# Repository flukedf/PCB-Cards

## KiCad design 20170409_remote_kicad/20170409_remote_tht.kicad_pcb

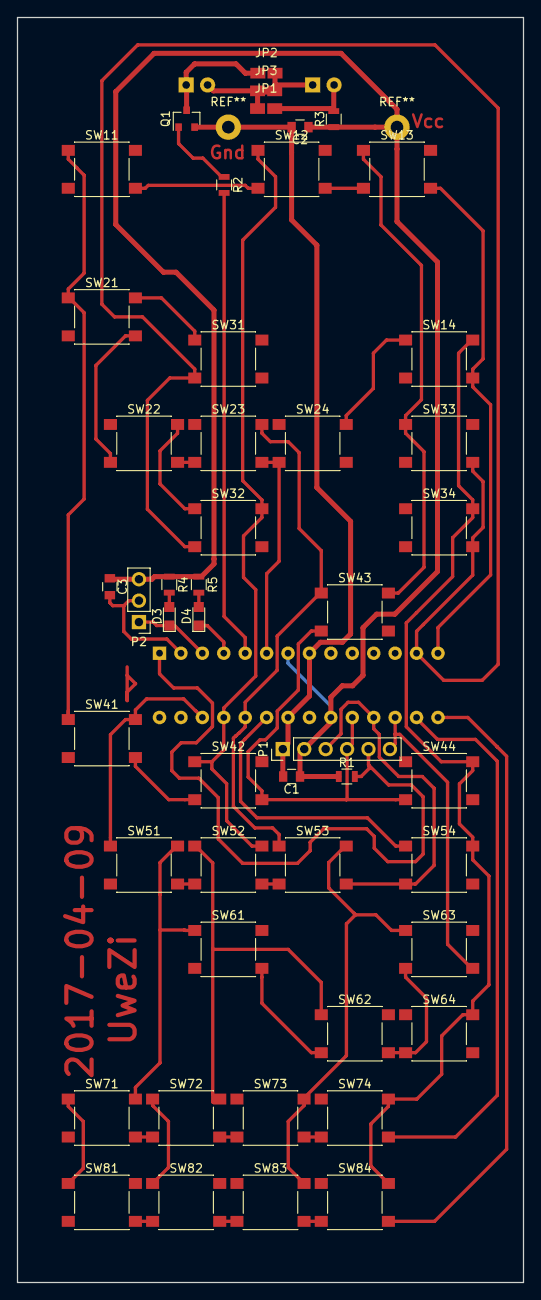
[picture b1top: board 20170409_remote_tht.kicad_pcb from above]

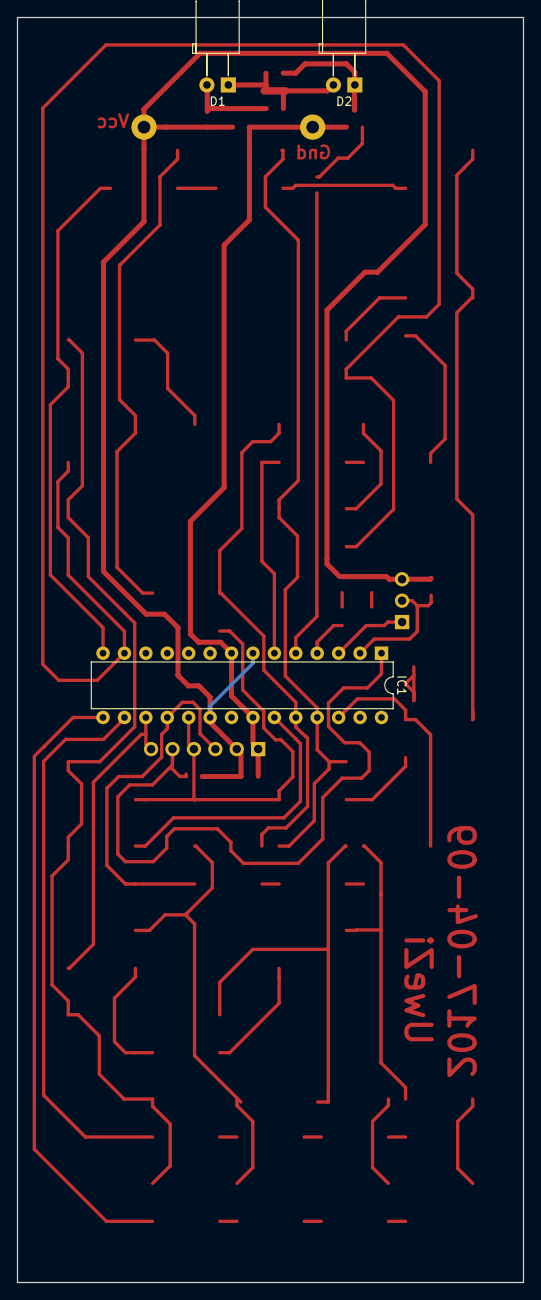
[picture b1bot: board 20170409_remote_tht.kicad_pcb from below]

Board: 2 copper layers, 60.0 x 150.0 mm, 51 parts (3 on the bottom side), 26 nets.

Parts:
C1, C2, C3: C; C_0805
D1, D2: LED; LED_D5.0mm_Horizontal_O3.81mm_Z3.0mm
D3, D4: LED; LED_0805
IC1: ATMEGA328-P; DIP-28_W7.62mm
JP1, JP2: Jumper_NO_Small; net_tie_open
JP3: Jumper_NC_Small; net_tie_closed
P1: CONN_01X06; Socket_Strip_Straight_1x06_Pitch2.54mm
P2: CONN_01X03; Socket_Strip_Straight_1x03_Pitch2.54mm
Q1: MMBT2222; SOT-23
R1, R2, R3, R4, R5: R; R_0805
SW11, SW12, SW13, SW14, SW21, SW22, SW23, SW24, SW31, SW32, SW33, SW34, SW41, SW42, SW43, SW44, SW51, SW52, SW53, SW54, SW61, SW62, SW63, SW64, SW71, SW72, SW73, SW74, SW81, SW82, SW83, SW84: SW_Push_45deg; SW_SPST_PTS645

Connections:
GND: C1.2, C2.2, IC1.8, IC1.22, P1.1, Q1.2
unnamed: D1.1, JP2.1, JP3.1
unnamed: D1.2, JP1.1, R3.2
unnamed: D2.1, JP2.2, Q1.3
unnamed: D2.2, JP1.2, JP3.2
unnamed: D3.2, R4.2
unnamed: D4.2, R5.2
unnamed: Q1.1, R2.1
PB0: IC1.14, SW11.2, SW12.2, SW13.2, SW14.2
PB1: IC1.15, SW81.2, SW82.2, SW83.2, SW84.2
PB2: IC1.16, SW71.2, SW72.2, SW73.2, SW74.2
PB3: IC1.17, P1.6, SW61.2, SW62.2, SW63.2, SW64.2
PB4: IC1.18, P1.3, SW51.2, SW52.2, SW53.2, SW54.2
PB5: IC1.19, P1.4, SW41.2, SW42.2, SW43.2, SW44.2
PC0: IC1.23, SW14.1, SW24.1, SW34.1, SW44.1, SW54.1, SW64.1, SW74.1, SW84.1
PC1: IC1.24, SW13.1, SW23.1, SW33.1, SW43.1, SW53.1, SW63.1, SW73.1, SW83.1
PC2: IC1.25, SW12.1, SW22.1, SW32.1, SW42.1, SW52.1, SW62.1, SW72.1, SW82.1
PC3: IC1.26, SW11.1, SW21.1, SW31.1, SW41.1, SW51.1, SW61.1, SW71.1, SW81.1
PD0: C3.2, IC1.2, P2.2
PD1: D3.1, IC1.3, P2.1
PD2: D4.1, IC1.4
PD3: IC1.5, R2.2
PD4: IC1.6, SW21.2, SW22.2, SW23.2, SW24.2
PD7: IC1.13, SW31.2, SW32.2, SW33.2, SW34.2
RESET: IC1.1, P1.5, R1.2
VCC: C1.1, C2.1, C3.1, IC1.7, IC1.20, P1.2, P2.3, R1.1, R3.1, R4.1, R5.1

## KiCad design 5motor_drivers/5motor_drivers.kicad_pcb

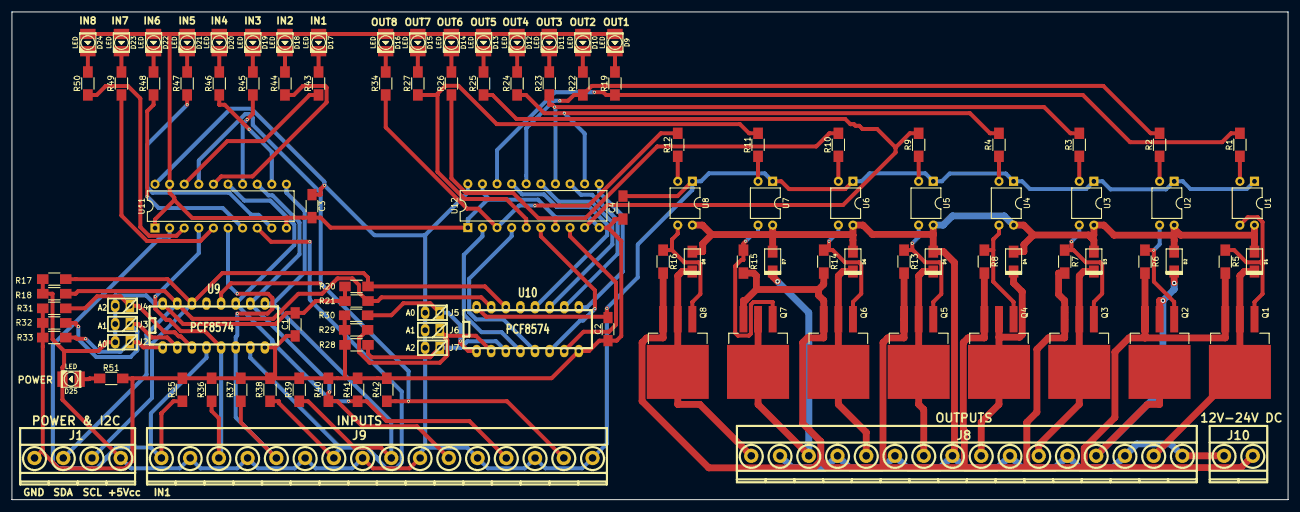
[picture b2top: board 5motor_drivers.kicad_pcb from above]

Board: 2 copper layers, 222.0 x 84.8 mm, 110 parts (0 on the bottom side), 85 nets.

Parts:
C1, C2, C3, C4: 100nF; C_1206_HandSoldering
D1, D2, D3, D4, D5, D6, D7, D8: D; do214ac
D9, D10, D11, D12, D13, D14, D15, D16, D17, D18, D19, D20, D21, D22, D23, D24, D25: LED; Led_PLCC2_3528
J1: POWER & I2C; mkds_1,5-4
J2, J5: A0; pin_strip_2
J3, J6: A1; pin_strip_2
J4, J7: A2; pin_strip_2
J8: OUTPUTS; mkds_1,5-16
J9: INPUTS; mkds_1,5-16
J10: 12V-24V DC; mkds_1,5-2
Q1, Q2, Q3, Q4, Q5, Q6, Q7, Q8: IRF540N; TO-263-3Lead
R1, R2, R3, R4, R9, R10, R11, R12: 470; R_1206_HandSoldering
R5, R6, R7, R8, R13, R14, R15, R16, R17, R18, R20, R21: 10K; R_1206_HandSoldering
R19, R22, R23, R24, R25, R26, R27, R34, R43, R44, R45, R46, R47, R48, R49, R50, R51: 330; R_1206_HandSoldering
R28, R29, R30, R31, R32, R33, R35, R36, R37, R38, R39, R40, R41, R42: 1K; R_1206_HandSoldering
U1, U2, U3, U4, U5, U6, U7, U8: PC817; DIP-4_W7.62mm
U9, U10: PCF8574; dil_16-300
U11, U12: 74LS244; DIP-20_W7.62mm

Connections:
+5Vcc: C1.2, C2.2, C3.1, C4.1, D25.2, J1.4, J2.2, J3.2, J4.2, J5.2, J6.2, J7.2, J9.2, J9.4, J9.6, J9.8, J9.10, J9.12, J9.14, J9.16, R17.1, R18.1, R20.1, R21.1, U1.1, U2.1, U3.1, U4.1, U5.1, U6.1, U7.1, U8.1, U9.16, U10.16, U11.20, U12.20
+24V: D1.1, D2.1, D3.1, D4.1, D5.1, D6.1, D7.1, D8.1, J8.2, J8.4, J8.6, J8.8, J8.10, J8.12, J8.14, J8.16, J10.1, U1.4, U2.4, U3.4, U4.4, U5.4, U6.4, U7.4, U8.4
GND: C1.1, C2.1, C3.2, C4.2, D9.1, D10.1, D11.1, D12.1, D13.1, D14.1, D15.1, D16.1, D17.1, D18.1, D19.1, D20.1, D21.1, D22.1, D23.1, D24.1, J1.1, R28.2, R29.2, R30.2, R31.2, R32.2, R33.2, R35.2, R36.2, R37.2, R38.2, R39.2, R40.2, R41.2, R42.2, R51.2, U9.8, U10.8, U11.1, U11.10, U11.19, U12.1, U12.10, U12.19
GNDPWR: J10.2, Q1.3, Q2.3, Q3.3, Q4.3, Q5.3, Q6.3, Q7.3, Q8.3, R5.2, R6.2, R7.2, R8.2, R13.2, R14.2, R15.2, R16.2
IN01: J9.1, R35.1, U9.4, U11.2
IN02: J9.3, R36.1, U9.5, U11.4
IN03: J9.5, R37.1, U9.6, U11.6
IN04: J9.7, R38.1, U9.7, U11.8
IN05: J9.9, R39.1, U9.9, U11.11
IN06: J9.11, R40.1, U9.10, U11.13
IN07: J9.13, R41.1, U9.11, U11.15
IN08: J9.15, R42.1, U9.12, U11.17
MOTOR_01-: D1.2, J8.15, Q1.2
MOTOR_02-: D2.2, J8.13, Q2.2
MOTOR_03-: D3.2, J8.11, Q3.2
MOTOR_04-: D4.2, J8.9, Q4.2
MOTOR_05-: D5.2, J8.7, Q5.2
MOTOR_06-: D6.2, J8.5, Q6.2
MOTOR_07-: D7.2, J8.3, Q7.2
MOTOR_08-: D8.2, J8.1, Q8.2
unnamed: D9.2, R19.2
unnamed: D10.2, R22.2
unnamed: D11.2, R23.2
unnamed: D12.2, R24.2
unnamed: D13.2, R25.2
unnamed: D14.2, R26.2
unnamed: D15.2, R27.2
unnamed: D16.2, R34.2
unnamed: D17.2, R43.2
unnamed: D18.2, R44.2
unnamed: D19.2, R45.2
unnamed: D20.2, R46.2
unnamed: D21.2, R47.2
unnamed: D22.2, R48.2
unnamed: D23.2, R49.2
unnamed: D24.2, R50.2
unnamed: D25.1, R51.1
unnamed: J2.1, R33.1, U9.1
unnamed: J3.1, R32.1, U9.2
unnamed: J4.1, R31.1, U9.3
unnamed: J5.1, R30.1, U10.1
unnamed: J6.1, R29.1, U10.2
unnamed: J7.1, R28.1, U10.3
unnamed: Q1.1, R5.1, U1.3
unnamed: Q2.1, R6.1, U2.3
unnamed: Q3.1, R7.1, U3.3
unnamed: Q4.1, R8.1, U4.3
unnamed: Q5.1, R13.1, U5.3
unnamed: Q6.1, R14.1, U6.3
unnamed: Q7.1, R15.1, U7.3
unnamed: Q8.1, R16.1, U8.3
unnamed: R1.1, U1.2
unnamed: R2.1, U2.2
unnamed: R3.1, U3.2
unnamed: R4.1, U4.2
unnamed: R9.1, U5.2
unnamed: R10.1, U6.2
unnamed: R11.1, U7.2
unnamed: R12.1, U8.2
Q1: R1.2, R19.1, U12.18
Q2: R2.2, R22.1, U12.16
Q3: R3.2, R23.1, U12.14
Q4: R4.2, R24.1, U12.12
Q5: R9.2, R25.1, U12.9
Q6: R10.2, R26.1, U12.7
Q7: R11.2, R27.1, U12.5
Q8: R12.2, R34.1, U12.3
S1: R43.1, U11.18
S2: R44.1, U11.16
S3: R45.1, U11.14
S4: R46.1, U11.12
S5: R47.1, U11.9
S6: R48.1, U11.7
S7: R49.1, U11.5
S8: R50.1, U11.3
SCL: J1.3, R17.2, R20.2, U9.14, U10.14
SDA: J1.2, R18.2, R21.2, U9.15, U10.15
SIGNAL_01: U10.4, U12.2
SIGNAL_02: U10.5, U12.4
SIGNAL_03: U10.6, U12.6
SIGNAL_04: U10.7, U12.8
SIGNAL_05: U10.9, U12.11
SIGNAL_06: U10.10, U12.13
SIGNAL_07: U10.11, U12.15
SIGNAL_08: U10.12, U12.17

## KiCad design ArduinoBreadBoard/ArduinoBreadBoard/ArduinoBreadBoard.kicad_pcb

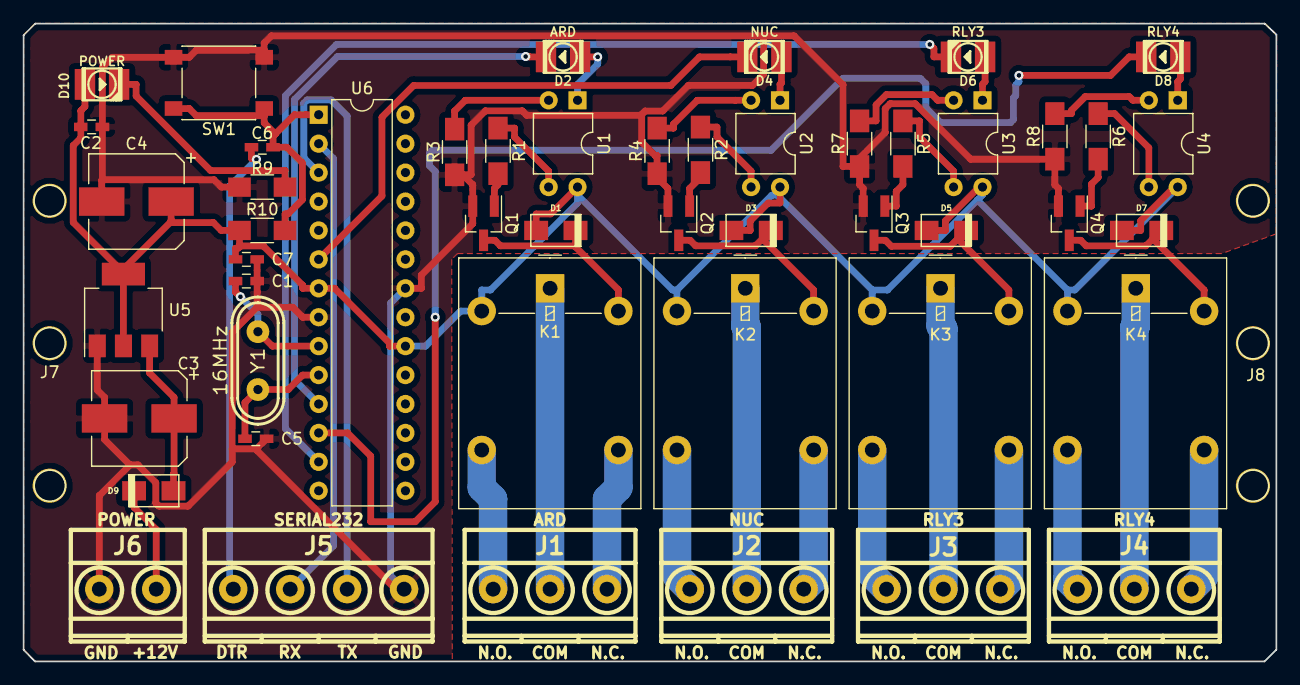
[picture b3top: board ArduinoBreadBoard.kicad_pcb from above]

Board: 2 copper layers, 110.0 x 56.0 mm, 51 parts (0 on the bottom side), 47 nets.

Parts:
C1, C5: 22pF; C_0603_HandSoldering
C2, C7: 100nF; C_0603_HandSoldering
C3, C4: 47uF; CP_Elec_8x6.5
C6: 0.1uF; C_0603_HandSoldering
D1, D3, D5, D7, D9: 1N4001; do214ac
D2: ARD; Led_PLCC2_3528
D4: NUC; Led_PLCC2_3528
D6: RLY3; Led_PLCC2_3528
D8: RLY4; Led_PLCC2_3528
D10: POWER; Led_PLCC2_3528
J1: ARD; mkds_1,5-3
J2: NUC; mkds_1,5-3
J3: RLY3; mkds_1,5-3
J4: RLY4; mkds_1,5-3
J5: SERIAL232; mkds_1,5-4
J6: POWER; mkds_1,5-2
J7, J8: hole; Bracket_RielDin_hole
K1, K2, K3, K4: JS1-5V-F
Q1, Q2, Q3, Q4: MMBT5551L; SOT-23_Handsoldering
R1, R2, R5, R6, R10: 10K; R_1206_HandSoldering
R3, R4, R7, R8: 1K; R_1206_HandSoldering
R9: 330; R_1206_HandSoldering
SW1: RESET; SW_SPST_PTS645
U1, U2, U3, U4: PC817; DIP-4_W7.62mm
U5: AMS1117-5.0; SOT-223-3Lead_TabPin2
U6: ATmega328P-PU; DIP-28_W7.62mm
Y1: 16MHz; crystal_hc-49s

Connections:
+5V: C2.1, C4.1, C7.1, D1.1, D3.1, D5.1, D7.1, D10.1, K1.2, K2.2, K3.2, K4.2, R10.1, U1.4, U2.4, U3.4, U4.4, U5.2, U6.7, U6.20
+12V: C3.1, D9.1, U5.3
D4: D4.2, U6.6
D5: D2.2, U6.11
D6: D8.2, U6.12
D7: D6.2, U6.13
DTR: C6.1, J5.1
GND: C1.1, C2.2, C3.2, C4.2, C5.1, C7.2, J5.4, J6.1, Q1.2, Q2.2, Q3.2, Q4.2, R3.1, R4.1, R7.1, R8.1, R9.2, SW1.2, U5.1, U6.8, U6.22
unnamed: C1.2, U6.9, Y1.1
unnamed: C5.2, U6.10, Y1.2
unnamed: C6.2, R10.2, SW1.1, U6.1
unnamed: D1.2, K1.5, Q1.3
unnamed: D2.1, U1.1
unnamed: D3.2, K2.5, Q2.3
unnamed: D4.1, U2.1
unnamed: D5.2, K3.5, Q3.3
unnamed: D6.1, U3.1
unnamed: D7.2, K4.5, Q4.3
unnamed: D8.1, U4.1
unnamed: D9.2, J6.2
unnamed: D10.2, R9.1
unnamed: J1.1, K1.3
unnamed: J1.2, K1.1
unnamed: J1.3, K1.4
unnamed: J2.1, K2.3
unnamed: J2.2, K2.1
unnamed: J2.3, K2.4
unnamed: J3.1, K3.3
unnamed: J3.2, K3.1
unnamed: J3.3, K3.4
unnamed: J4.1, K4.3
unnamed: J4.2, K4.1
unnamed: J4.3, K4.4
unnamed: Q1.1, R1.2
unnamed: Q2.1, R2.2
unnamed: Q3.1, R5.2
unnamed: Q4.1, R6.2
unnamed: R1.1, U1.3
unnamed: R2.1, U2.3
unnamed: R3.2, U1.2
unnamed: R4.2, U2.2
unnamed: R5.1, U3.3
unnamed: R6.1, U4.3
unnamed: R7.2, U3.2
unnamed: R8.2, U4.2
Rx: J5.2, U6.2
Tx: J5.3, U6.3

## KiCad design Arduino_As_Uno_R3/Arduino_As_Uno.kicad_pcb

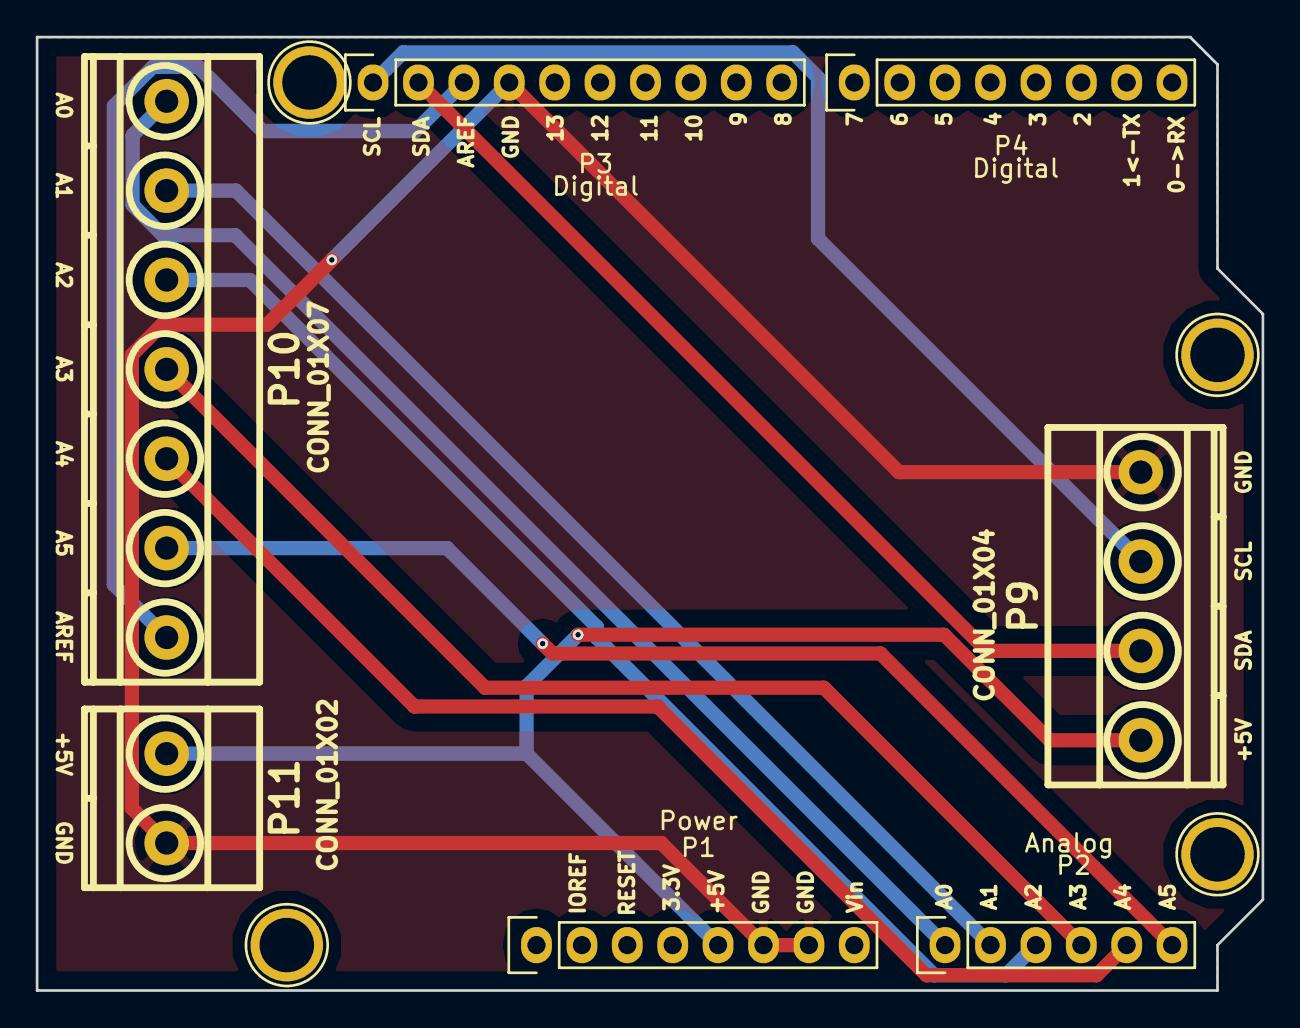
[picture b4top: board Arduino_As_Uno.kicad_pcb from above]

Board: 2 copper layers, 68.6 x 53.3 mm, 11 parts (0 on the bottom side), 11 nets.

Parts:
P1: Power; Socket_Strip_Arduino_1x08
P2: Analog; Socket_Strip_Arduino_1x06
P3: Digital; Socket_Strip_Arduino_1x10
P4: Digital; Socket_Strip_Arduino_1x08
P5, P6, P7, P8: CONN_01X01; Arduino_1pin
P9: CONN_01X04; mkds_1,5-4
P10: CONN_01X07; mkds_1,5-7
P11: CONN_01X02; mkds_1,5-2

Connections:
+5V: P1.5, P9.1, P11.1
/(SCL): P3.1, P9.3
/(SDA): P3.2, P9.2
/A0: P2.1, P10.1
/A1: P2.2, P10.2
/A2: P2.3, P10.3
/A3: P2.4, P10.4
/A4: P2.5, P10.5
/A5: P2.6, P10.6
/AREF: P3.3, P10.7
GND: P1.6, P1.7, P3.4, P9.4, P11.2

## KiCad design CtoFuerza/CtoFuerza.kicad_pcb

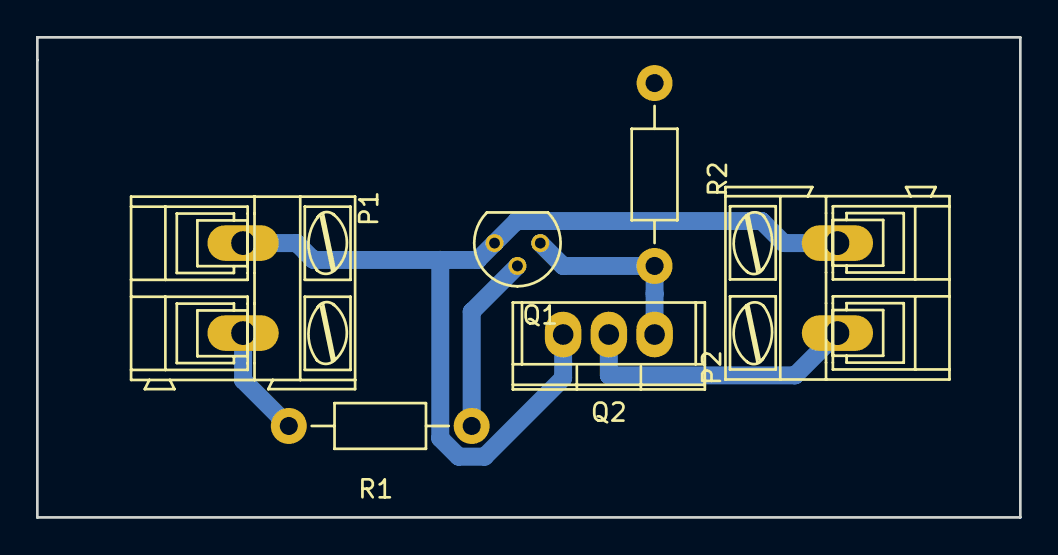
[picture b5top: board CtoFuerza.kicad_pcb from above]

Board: 2 copper layers, 54.6 x 26.7 mm, 6 parts (0 on the bottom side), 5 nets.

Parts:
P1, P2: CONN_01X02; AK300-2
Q1: BC548; TO-92_Molded_Narrow
Q2: IRF540N; TO-220
R1, R2: R; Resistor_Horizontal_RM10mm

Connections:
GND: P1.1, P2.2, Q1.3, Q2.3
unnamed: P1.2, R1.2
unnamed: P2.1, Q2.2
unnamed: Q1.1, Q2.1, R2.2
unnamed: Q1.2, R1.1

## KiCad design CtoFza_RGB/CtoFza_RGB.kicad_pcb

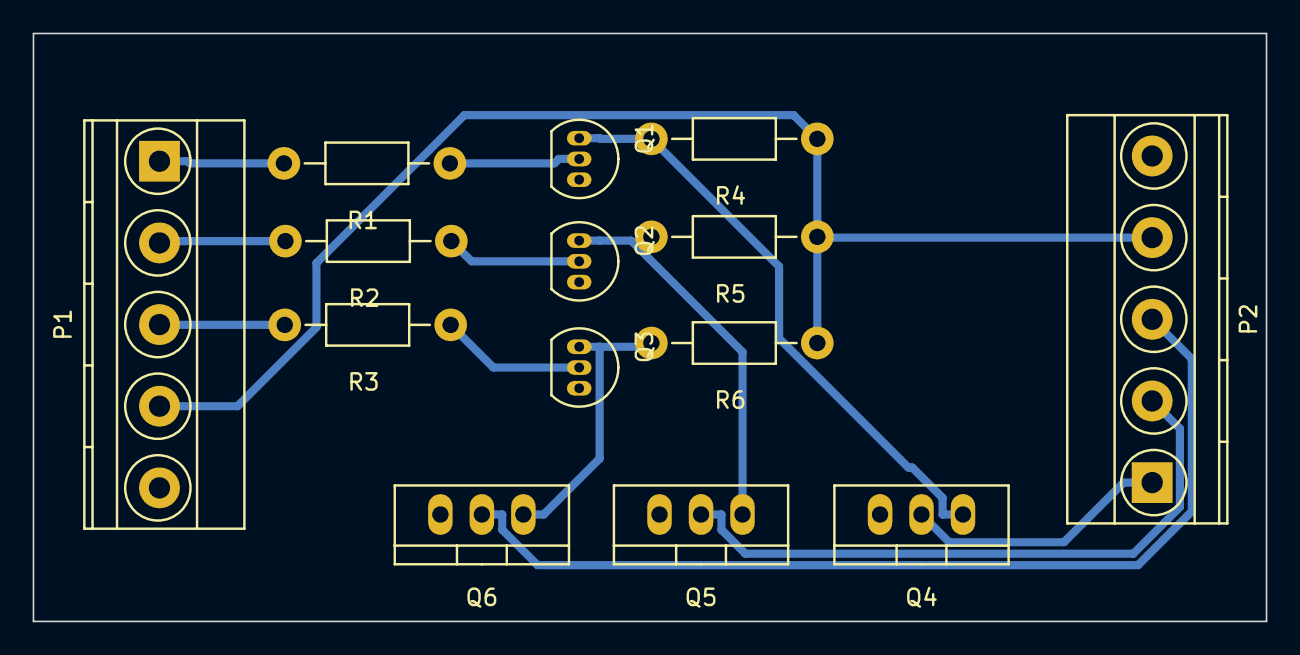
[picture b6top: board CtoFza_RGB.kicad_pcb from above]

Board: 2 copper layers, 75.5 x 36.0 mm, 14 parts (0 on the bottom side), 14 nets.

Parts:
P1: INPUT; TerminalBlock_Pheonix_MKDS1.5-5pol
P2: OUTPUT; TerminalBlock_Pheonix_MKDS1.5-5pol
Q1, Q2, Q3: BC548; TO-92_Inline_Narrow_Oval
Q4, Q5, Q6: IRF540N; TO-220_Neutral123_Vertical
R1, R2, R3, R4, R5, R6: 10K; Resistor_Horizontal_RM10mm

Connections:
12VCD: P1.4, P2.4, R4.1, R5.1, R6.1
B_IN: P1.3, R3.2
B_OUT: P2.3, Q6.2
GND: P1.5, P2.5, Q1.3, Q2.3, Q3.3, Q4.3, Q5.3, Q6.3
G_IN: P1.2, R2.2
G_OUT: P2.2, Q5.2
unnamed: Q1.1, Q4.1, R4.2
unnamed: Q1.2, R1.1
unnamed: Q2.1, Q5.1, R5.2
unnamed: Q2.2, R2.1
unnamed: Q3.1, Q6.1, R6.2
unnamed: Q3.2, R3.1
R_IN: P1.1, R1.2
R_OUT: P2.1, Q4.2

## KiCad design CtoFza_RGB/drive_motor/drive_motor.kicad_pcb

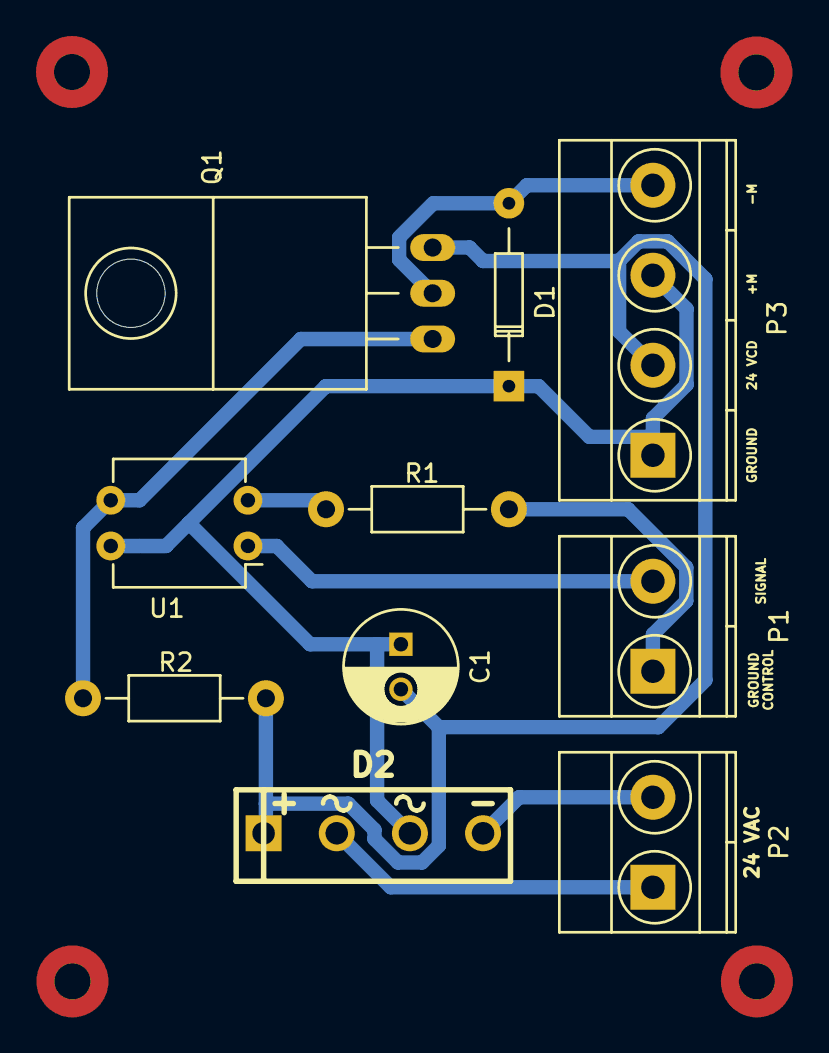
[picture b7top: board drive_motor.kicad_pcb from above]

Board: 2 copper layers, 14 parts (0 on the bottom side), 9 nets.

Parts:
C1: 100uF; C_Radial_D6.3_L11.2_P2.5
D1: 1N4001; Diode_DO-35_SOD27_Horizontal_RM10
D2: KPB206; bridge_2KBP
HOLE-M2, HOLE-M2#2, HOLE-M2#3, HOLE-M2#4: VAL**; HOLE-M2-COND
P1, P2: CONN_01X02; TerminalBlock_Pheonix_MKDS1.5-2pol
P3: CONN_01X04; TerminalBlock_Pheonix_MKDS1.5-4pol
Q1: IRF540N; TO-220_Neutral123_Horizontal
R1: 470; Resistor_Horizontal_RM10mm
R2: 10K; Resistor_Horizontal_RM10mm
U1: PC817; DIP-4_W7.62mm

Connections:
GND: C1.2, D2.1, P3.2, Q1.3, R2.2
GND_CTRL: P1.1, R1.2
MOTOR+: C1.1, D1.1, D2.3, P3.1, P3.3, U1.4
MOTOR-: D1.2, P3.4, Q1.2
unnamed: D2.2, P2.1
unnamed: D2.4, P2.2
unnamed: Q1.1, R2.1, U1.3
unnamed: R1.1, U1.2
SIGNAL: P1.2, U1.1

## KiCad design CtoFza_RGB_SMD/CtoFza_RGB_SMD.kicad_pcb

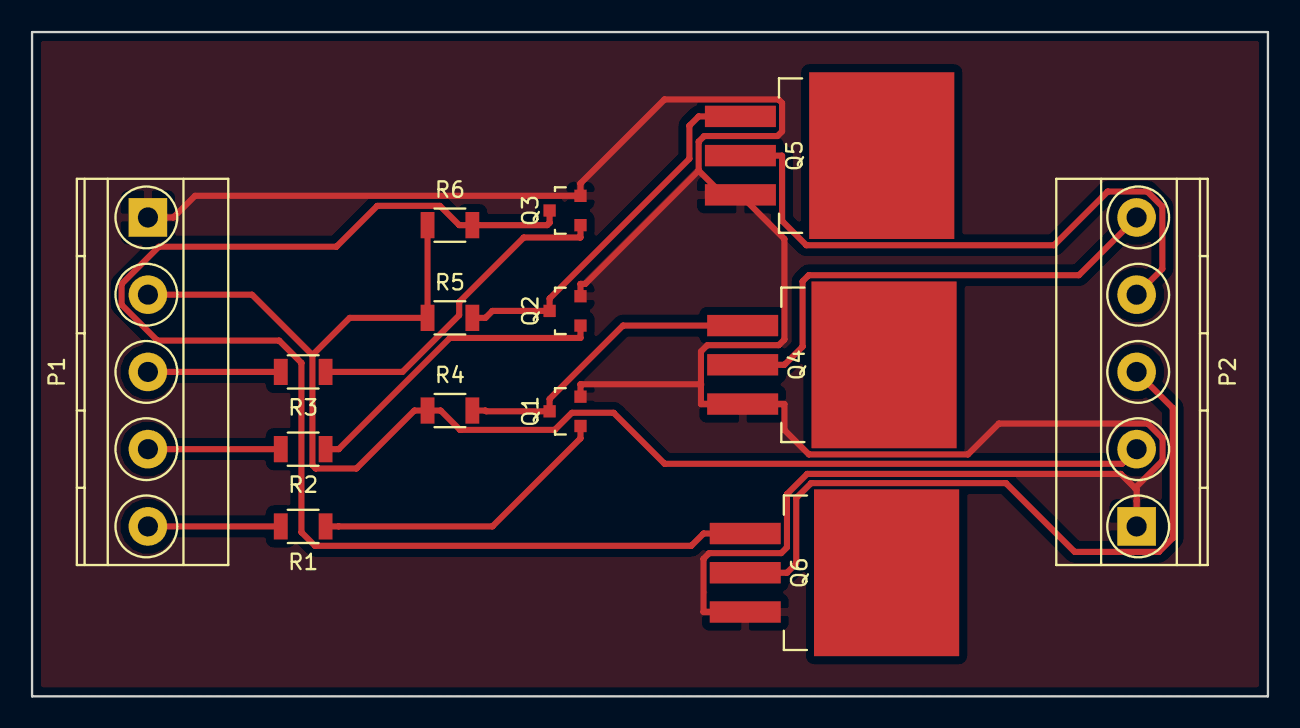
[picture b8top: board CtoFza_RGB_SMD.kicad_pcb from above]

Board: 2 copper layers, 80.0 x 43.0 mm, 14 parts (0 on the bottom side), 14 nets.

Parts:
P1: INPUT; TerminalBlock_Pheonix_MKDS1.5-5pol
P2: OUTPUT; TerminalBlock_Pheonix_MKDS1.5-5pol
Q1, Q2, Q3: BC848; SOT-23
Q4, Q5, Q6: IRF540N; TO-263-3Lead
R1, R2, R3, R4, R5, R6: 10K; R_1206

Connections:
12VCD: P1.2, P2.2, R4.1, R5.1, R6.1
B_IN: P1.3, R3.2
B_OUT: P2.3, Q6.2
GND: P1.1, P2.1, Q1.2, Q2.2, Q3.2, Q4.3, Q5.3, Q6.3
G_IN: P1.4, R2.2
G_OUT: P2.4, Q5.2
unnamed: Q1.1, R1.1
unnamed: Q1.3, Q4.1, R4.2
unnamed: Q2.1, R2.1
unnamed: Q2.3, Q5.1, R5.2
unnamed: Q3.1, R3.1
unnamed: Q3.3, Q6.1, R6.2
R_IN: P1.5, R1.2
R_OUT: P2.5, Q4.2
